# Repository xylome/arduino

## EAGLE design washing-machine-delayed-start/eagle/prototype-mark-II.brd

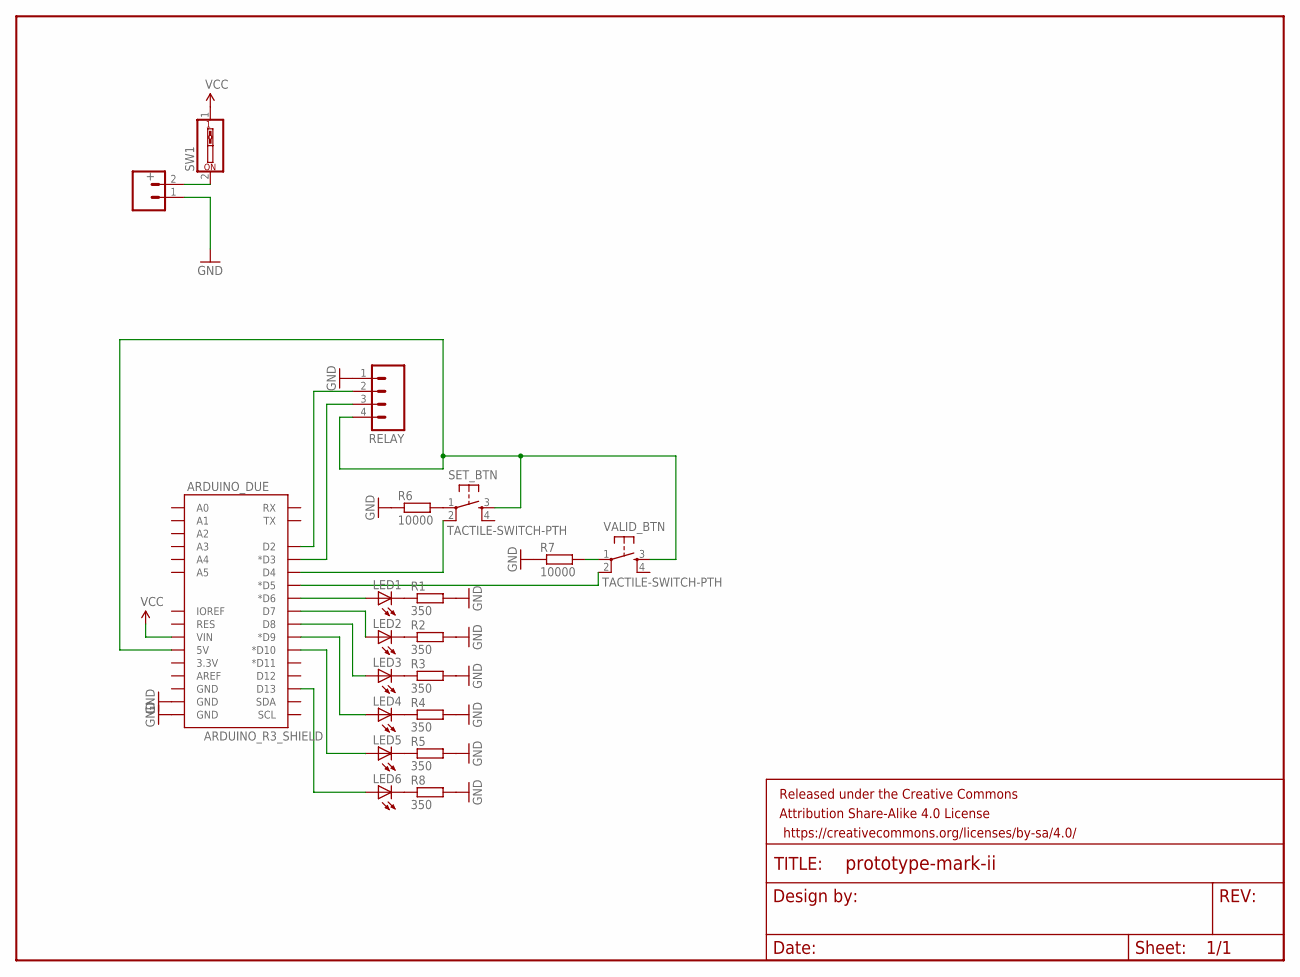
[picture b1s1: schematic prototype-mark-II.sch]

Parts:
+: M02PTH; 1X02
ARDUINO_DUE: ARDUINO_R3_SHIELD; UNO_R3_SHIELD
FRAME1: FRAME-LETTERNO_PACKAGE; DUMMY
LED1, LED2, LED3, LED4, LED5, LED6: LED3MM
R1, R2, R3, R4, R5, R8: 350; 0204/7
R6, R7: 10000; 0204/7
RELAY: M04PTH; 1X04
SET_BTN: TACTILE-SWITCH-PTH; TAC-SWITCH-PTH
SW1: SW_DIP-1; EDG-01
VALID_BTN: TACTILE-SWITCH-PTH; TAC-SWITCH-PTH

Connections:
GND: +.1, ARDUINO_DUE.GND@0 (GND), ARDUINO_DUE.GND@1 (GND), R1.2, R2.2, R3.2, R4.2, R5.2, R6.1, R7.1, R8.2, RELAY.1
unnamed: ARDUINO_DUE.D6 (*D6), LED1.A
unnamed: LED1.K (C), R1.1
unnamed: ARDUINO_DUE.D7, LED2.A
unnamed: LED2.K (C), R2.1
unnamed: ARDUINO_DUE.D8, LED3.A
unnamed: ARDUINO_DUE.D9 (*D9), LED4.A
unnamed: ARDUINO_DUE.D10 (*D10), LED5.A
unnamed: LED3.K (C), R3.1
unnamed: LED4.K (C), R4.1
unnamed: LED5.K (C), R5.1
unnamed: R6.2, SET_BTN.1
unnamed: ARDUINO_DUE.D5 (*D5), VALID_BTN.2
unnamed: ARDUINO_DUE.5V, RELAY.4, SET_BTN.3, VALID_BTN.3
unnamed: R7.2, VALID_BTN.1
unnamed: ARDUINO_DUE.D4, SET_BTN.2
unnamed: +.2, SW1.2
unnamed: LED6.K (C), R8.1
unnamed: ARDUINO_DUE.D13, LED6.A
unnamed: ARDUINO_DUE.D3 (*D3), RELAY.3
unnamed: ARDUINO_DUE.D2, RELAY.2
VCC: ARDUINO_DUE.VIN, SW1.1

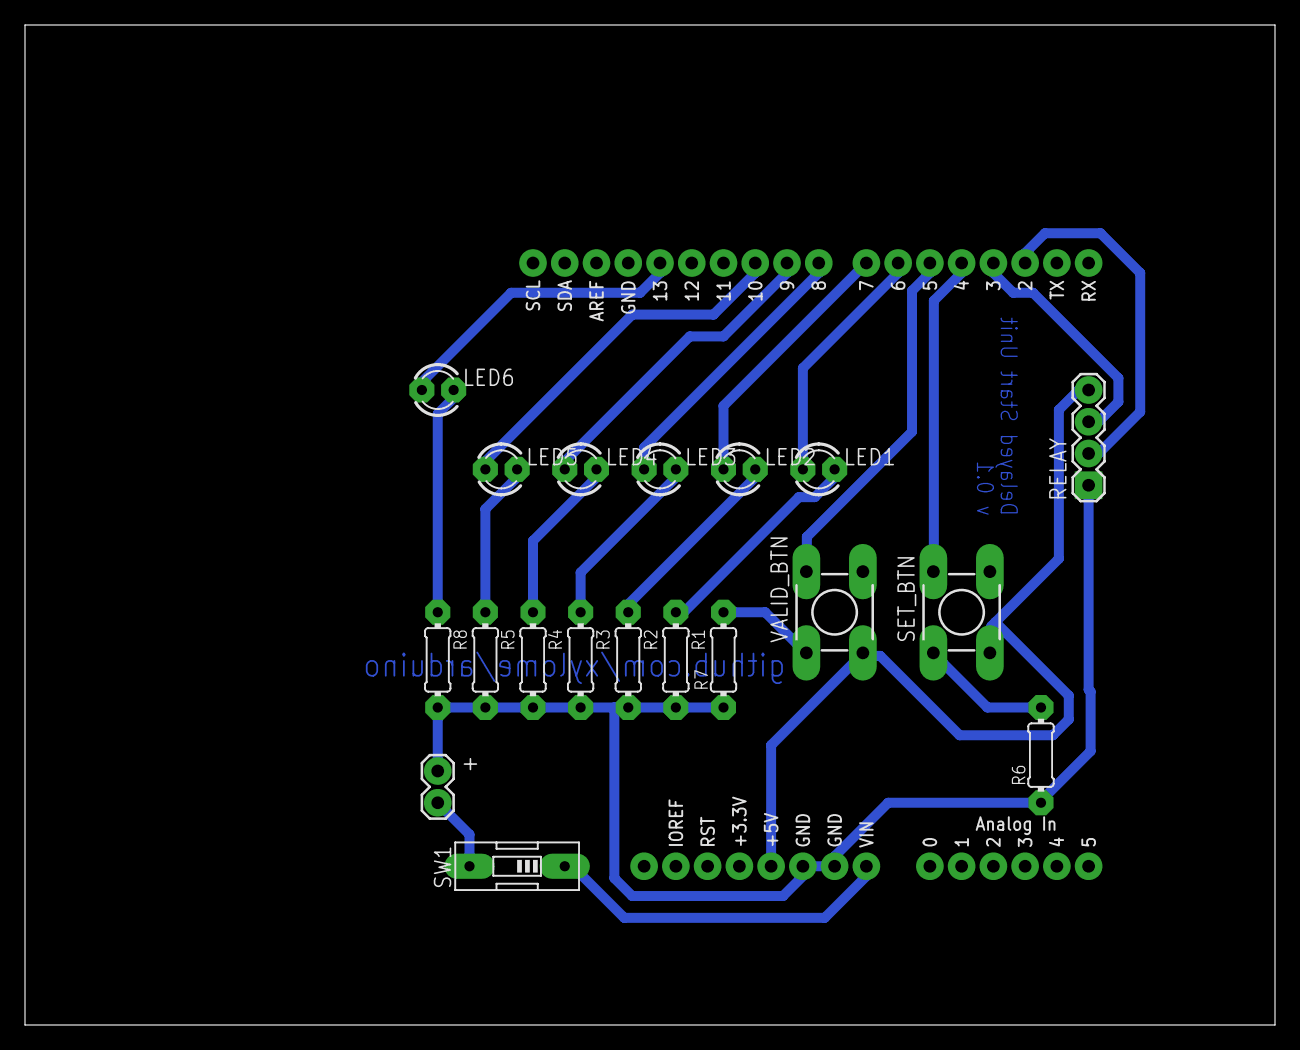
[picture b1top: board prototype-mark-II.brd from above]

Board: 2 copper layers, 100.0 x 80.0 mm, 21 parts (0 on the bottom side), 22 nets.

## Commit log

2016-08-04 Working with button bounce
2016-08-04 Working prototype with delays
2016-08-06 Add bargraph and code clean
2016-08-06 Add first fritzing prototype
2016-08-07 Trying to route…
2016-08-08 Add eagle files
2016-08-08 Routes improvement
2016-08-08 Swap relay states (strange), adjust timings when talking to the machine
2016-08-09 Nice routing
2016-08-09 Reverse 4 PIN header for the relay
2016-10-26 Update : pin connection adjustments and delay between on/off start/stop increased

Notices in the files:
parts and their libraries:
SparkFun-Boards: Licensing: Creative Commons ShareAlike 4.0 International - https://creativecommons.org/licenses/by-sa/4.0
SparkFun-Aesthetics: Released under the Creative Commons Attribution Share-Alike 4.0 License
SparkFun-Aesthetics: https://creativecommons.org/licenses/by-sa/4.0
